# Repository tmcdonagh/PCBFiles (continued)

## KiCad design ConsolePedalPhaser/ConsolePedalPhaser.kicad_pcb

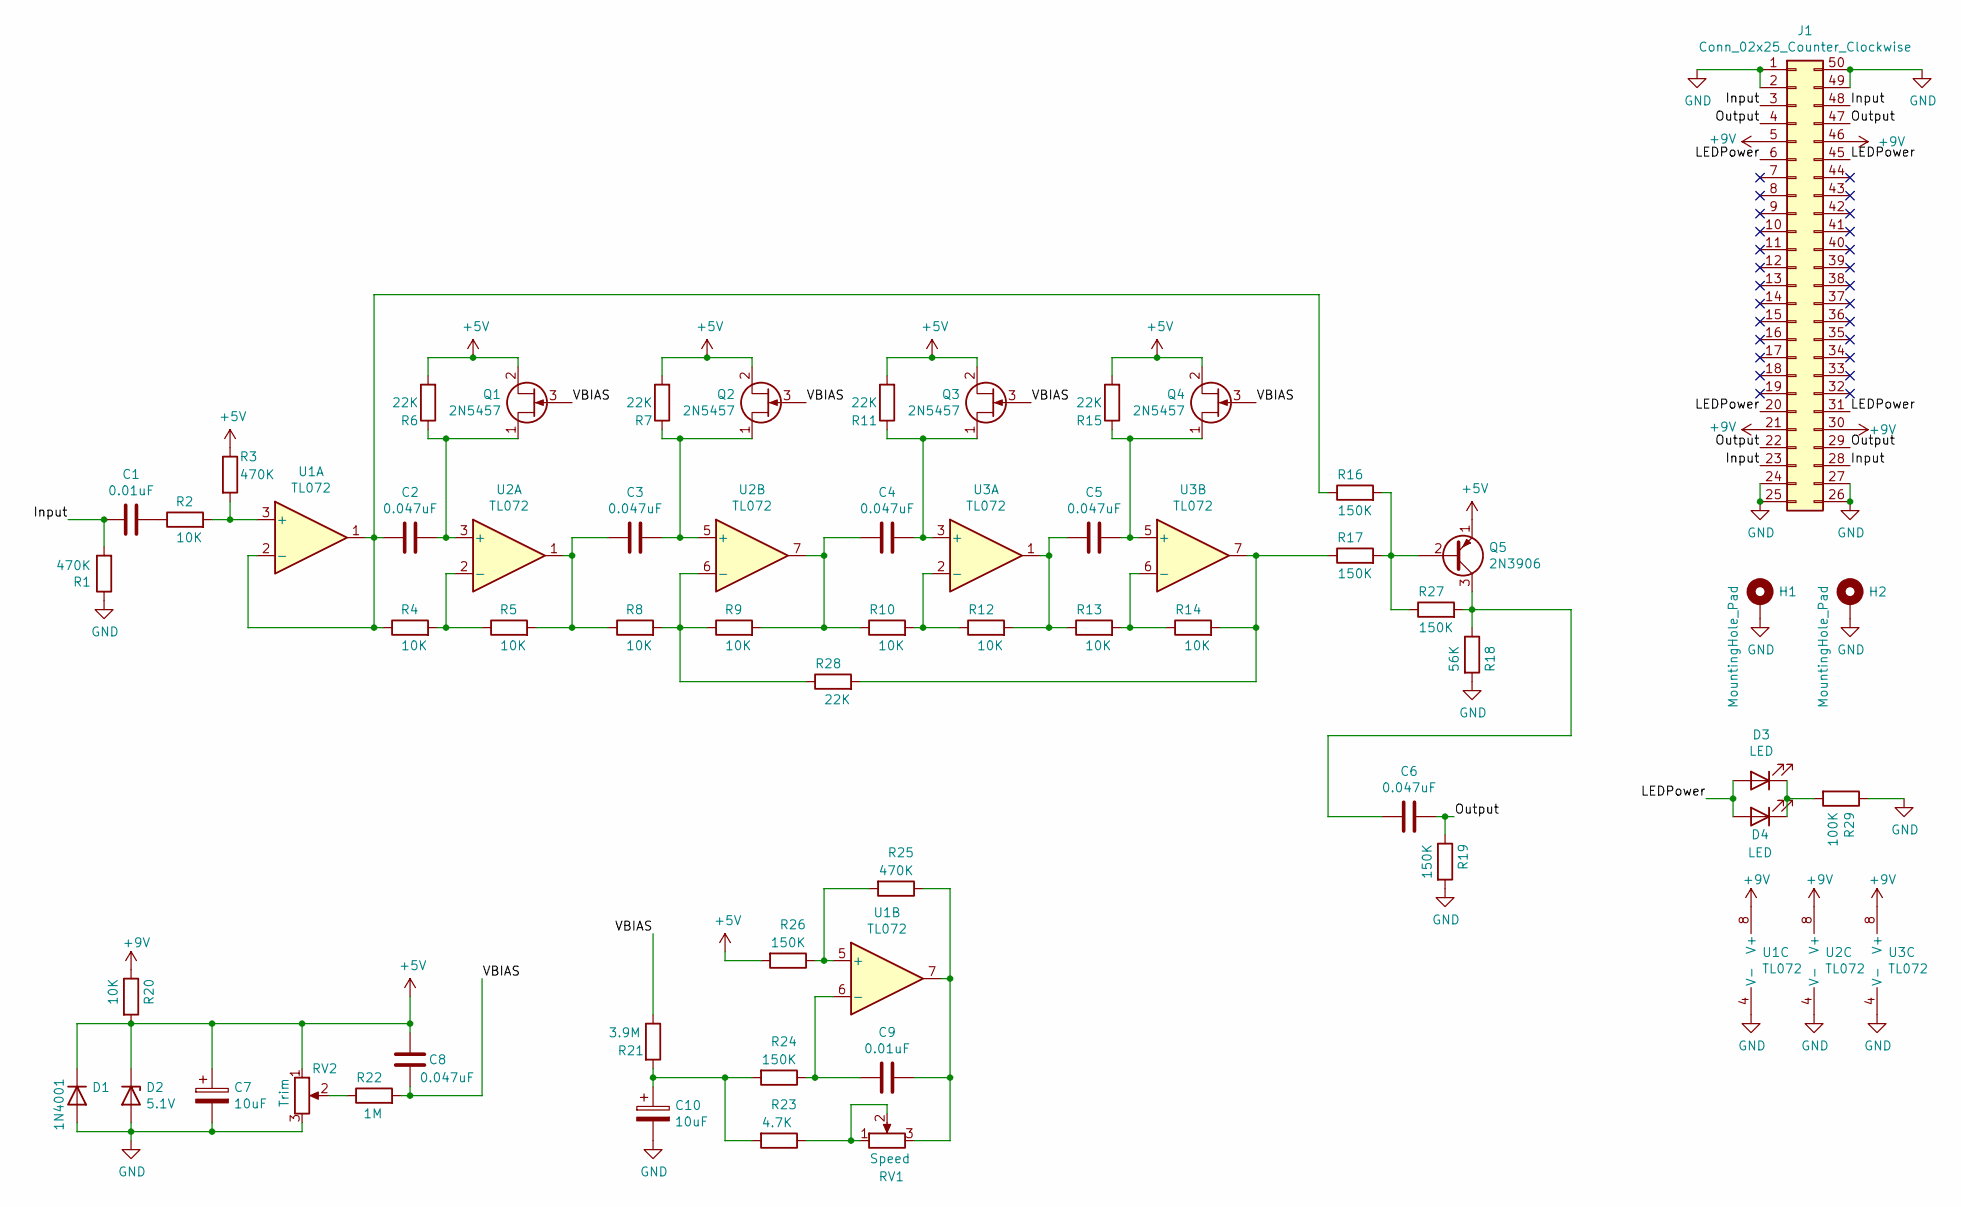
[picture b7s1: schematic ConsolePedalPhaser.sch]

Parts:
C1, C9: 0.01uF; C_Flat_L7.2_H6.5
C2, C3, C4, C5, C6, C8: 0.047uF; C_Flat_L7.2_H6.5
C7, C10: 10uF; CP_Radial_D6.3mm_P2.50mm_L11.0mm
D1: 1N4001; D_DO-41_SOD81_P10.16mm_Horizontal
D2: 5.1V; D_DO-35_SOD27_P7.62mm_Horizontal
D3, D4: LED; LED_D5.0mm
H1, H2: MountingHole_Pad; MountingHole_2.5mm_Pad
J1: Conn_02x25_Counter_Clockwise; N64-Connector
Q1, Q2, Q3, Q4: 2N5457; TO-92_Inline
Q5: 2N3906; TO-92_Inline
R1, R3, R25: 470K; R_Axial_DIN0207_L6.3mm_D2.5mm_P10.16mm_Horizontal
R2, R4, R5, R8, R9, R10, R12, R13, R14, R20: 10K; R_Axial_DIN0207_L6.3mm_D2.5mm_P10.16mm_Horizontal
R6, R7, R11, R15, R28: 22K; R_Axial_DIN0207_L6.3mm_D2.5mm_P10.16mm_Horizontal
R16, R17, R19, R24, R26, R27: 150K; R_Axial_DIN0207_L6.3mm_D2.5mm_P10.16mm_Horizontal
R18: 56K; R_Axial_DIN0207_L6.3mm_D2.5mm_P10.16mm_Horizontal
R21: 3.9M; R_Axial_DIN0207_L6.3mm_D2.5mm_P10.16mm_Horizontal
R22: 1M; R_Axial_DIN0207_L6.3mm_D2.5mm_P10.16mm_Horizontal
R23: 4.7K; R_Axial_DIN0207_L6.3mm_D2.5mm_P10.16mm_Horizontal
R29: 100K; R_Axial_DIN0207_L6.3mm_D2.5mm_P10.16mm_Horizontal
RV1: Speed; Potentiometer_Bourns_PTV09A-1_Single_Vertical
RV2: Trim; Potentiometer_Bourns_3386F_Vertical
U1, U2, U3: TL072; DIP-8_W7.62mm_Socket

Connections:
+5V: C7.1, C8.1, D1.1 (K), D2.1 (K), Q1.2 (S), Q2.2 (S), Q3.2 (S), Q4.2 (S), Q5.1 (E), R3.1, R6.2, R7.2, R11.2, R15.2, R20.2, R26.2, RV2.1
+9V: J1.5, J1.21, J1.30, J1.46, R20.1, U1.8 (V+), U2.8 (V+), U3.8 (V+)
/Input: C1.2, J1.3, J1.23, J1.28, J1.48, R1.2
/LEDPower: D3.2 (A), D4.2 (A), J1.6, J1.20, J1.31, J1.45
/Output: C6.1, J1.4, J1.22, J1.29, J1.47, R19.1
/VBIAS: C8.2, Q1.3 (G), Q2.3 (G), Q3.3 (G), Q4.3 (G), R21.1, R22.2
GND: C7.2, C10.2, D1.2 (A), D2.2 (A), H1.1, H2.1, J1.1, J1.2, J1.24, J1.25, J1.26, J1.27, J1.49, J1.50, R1.1, R18.2, R19.2, R29.1, RV2.3, U1.4 (V-), U2.4 (V-), U3.4 (V-)
unnamed: C1.1, R2.1
unnamed: C2.1, Q1.1 (D), R6.1, U2.3 (+)
unnamed: C2.2, R4.1, R16.1, U1.1, U1.2 (-)
unnamed: C3.1, Q2.1 (D), R7.1, U2.5 (+)
unnamed: C3.2, R5.2, R8.1, U2.1
unnamed: C4.1, Q3.1 (D), R11.1, U3.3 (+)
unnamed: C4.2, R9.2, R10.1, U2.7
unnamed: C5.1, Q4.1 (D), R15.1, U3.5 (+)
unnamed: C5.2, R12.2, R13.1, U3.1
unnamed: C6.2, Q5.3 (C), R18.1, R27.2
unnamed: C9.1, R25.1, RV1.3, U1.7
unnamed: C9.2, R24.1, U1.6 (-)
unnamed: C10.1, R21.2, R23.2, R24.2
unnamed: D3.1 (K), D4.1 (K), R29.2
unnamed: Q5.2 (B), R16.2, R17.2, R27.1
unnamed: R2.2, R3.2, U1.3 (+)
unnamed: R4.2, R5.1, U2.2 (-)
unnamed: R10.2, R12.1, U3.2 (-)
unnamed: R13.2, R14.1, U3.6 (-)
unnamed: R14.2, R17.1, R28.2, U3.7
unnamed: R22.1, RV2.2
unnamed: R23.1, RV1.1, RV1.2
unnamed: R25.2, R26.1, U1.5 (+)
unnamed: R8.2, R9.1, R28.1, U2.6 (-)

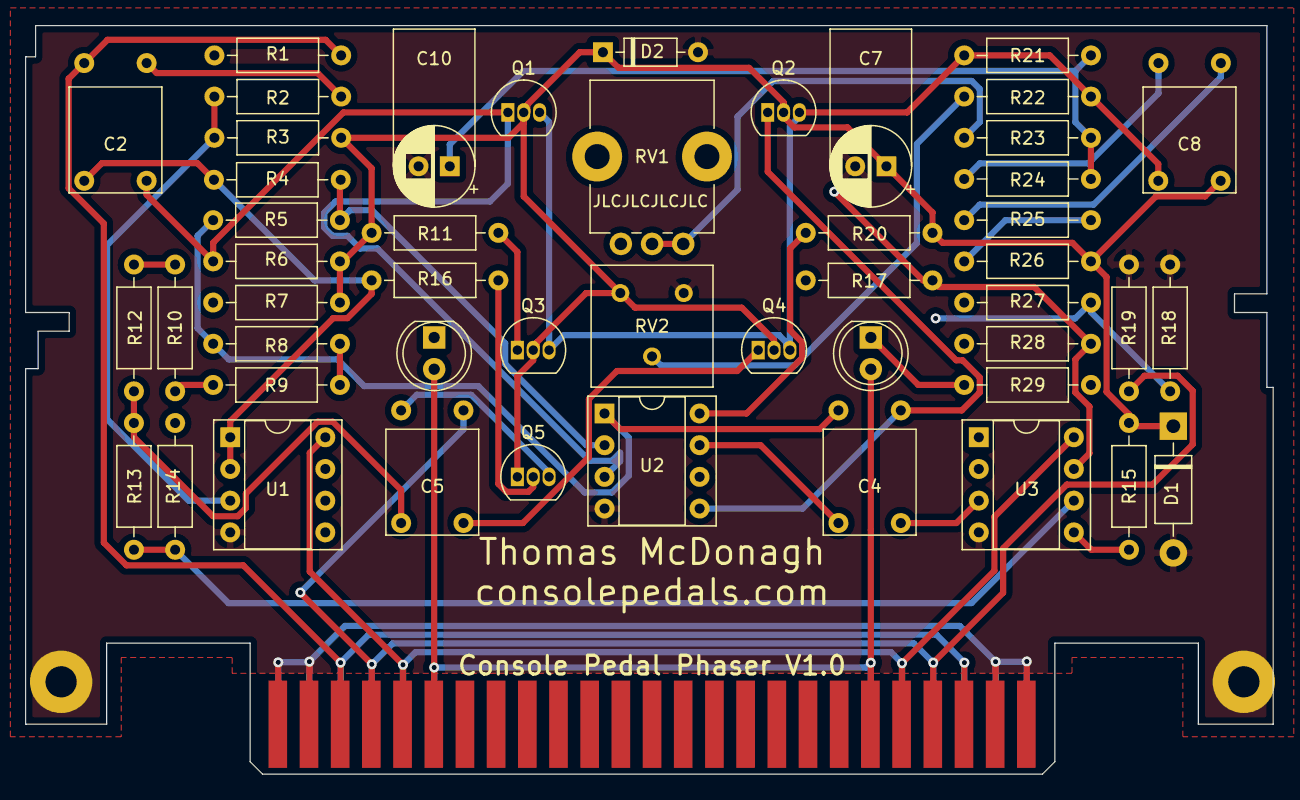
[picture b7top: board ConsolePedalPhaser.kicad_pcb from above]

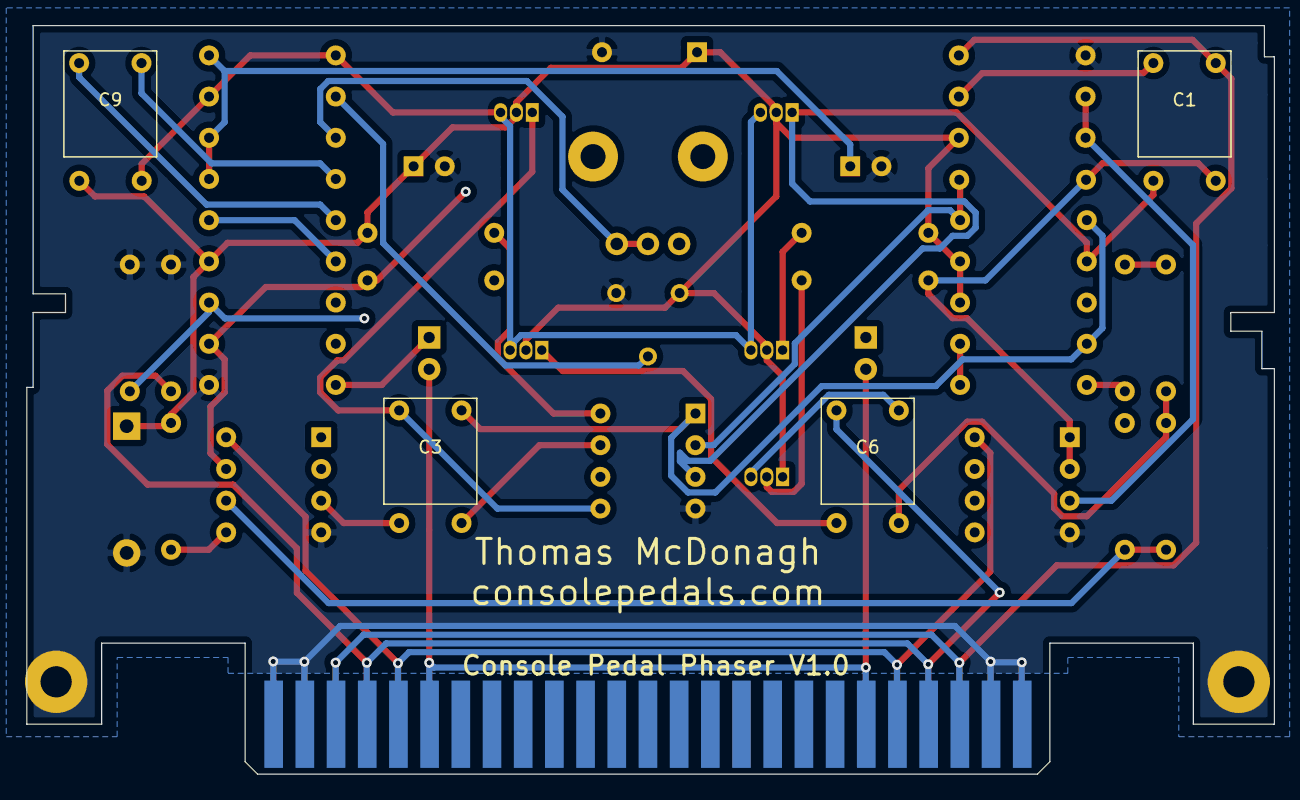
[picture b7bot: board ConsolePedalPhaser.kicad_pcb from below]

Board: 4 copper layers, 100.0 x 60.0 mm, 56 parts (4 on the bottom side), 31 nets.

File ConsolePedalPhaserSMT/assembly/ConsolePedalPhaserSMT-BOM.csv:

Comment,Designator,Footprint,LCSC
0.01uF,"C1,C9",Capacitor_SMD:C_0603_1608Metric,C57112
0.047uF,"C2,C3,C4,C5,C6,C8",Capacitor_SMD:C_0603_1608Metric,C1622
10uF,"C7,C10",Capacitor_SMD:CP_Elec_5x5.3,C249452
1N4001,D1,Diode_SMD:D_SOD-123,C162732
5.1V,D2,Diode_SMD:D_SOD-323,C489146
470K,"R1,R3,R25",Resistor_SMD:R_0603_1608Metric,C23178
56K,R18,Resistor_SMD:R_0603_1608Metric,C23206
10K,"R2,R4,R5,R8,R9,R10,R12,R13,R14,R20",Resistor_SMD:R_0603_1608Metric,C25804
3.9M,R21,Resistor_SMD:R_0603_1608Metric,C23019
1M,R22,Resistor_SMD:R_0603_1608Metric,C22935
4.7K,R23,Resistor_SMD:R_0603_1608Metric,C23162
150K,"R16,R17,R19,R24,R26,R27",Resistor_SMD:R_0603_1608Metric,C22807
22K,"R6,R7,R11,R15,R28",Resistor_SMD:R_0603_1608Metric,C31850
TL072,"U1,U2,U3",Package_SO:SOIC-8_3.9x4.9mm_P1.27mm,C6961
